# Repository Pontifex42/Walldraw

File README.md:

# Walldraw
Vollständige Anleitung auf Deutsch ist in "Wandplotter.pdf".
Find a german manual in the file "Wandplotter.pdf".

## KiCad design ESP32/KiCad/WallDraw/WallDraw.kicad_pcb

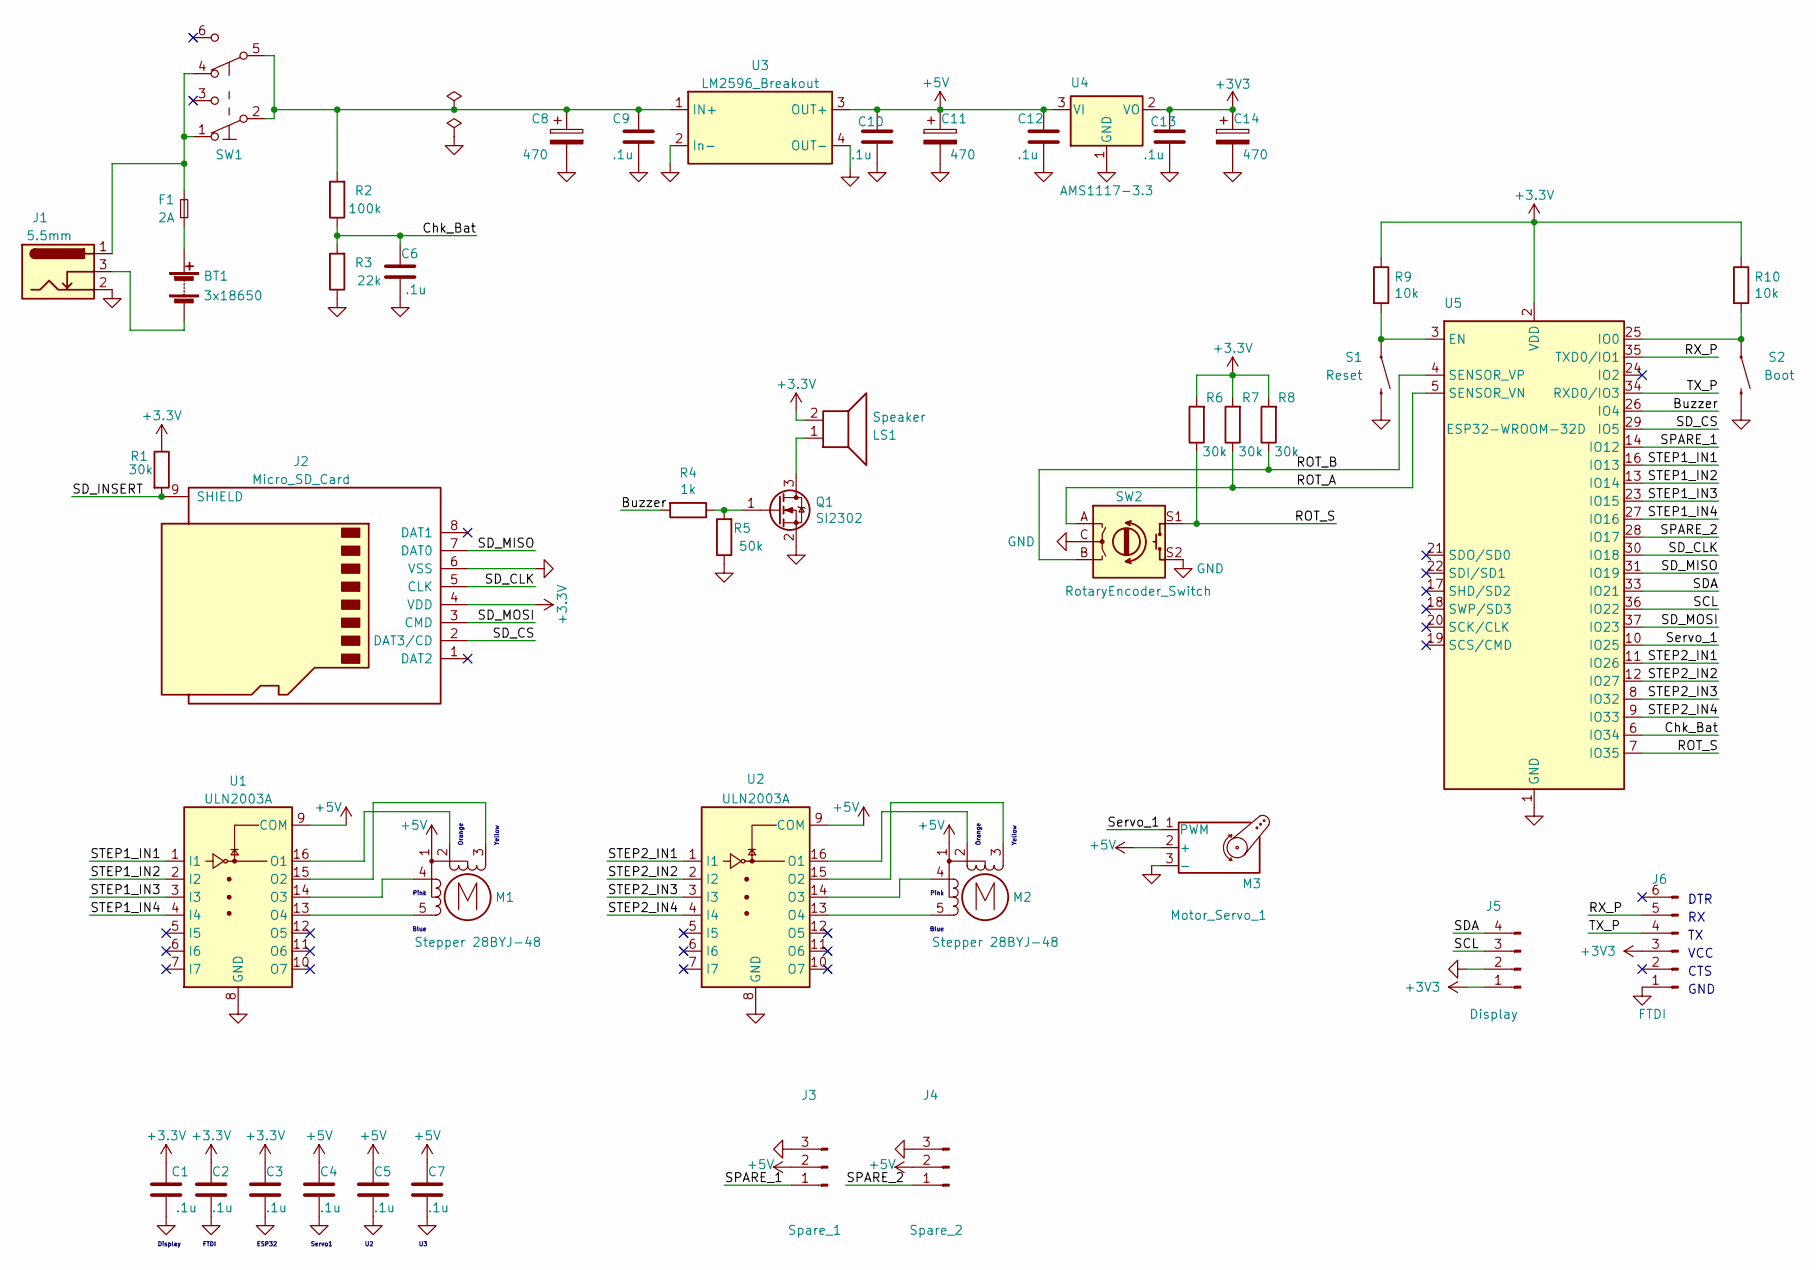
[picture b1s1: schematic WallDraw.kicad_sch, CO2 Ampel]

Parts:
BT1: 3x18650; LiIo18650x3_PCB_Mount
C1, C2, C3, C4, C5, C6, C7, C9, C10, C12, C13: .1u; C_0805_2012Metric_Pad1.18x1.45mm_HandSolder
C8, C11, C14: 470; CP_Elec_8x10.5
F1: 2A; Fuse_1206_3216Metric_Pad1.42x1.75mm_HandSolder
J1: 5.5mm; BarrelJack_Horizontal
J2: Micro_SD_Card; GCT-MEM2055-00-190-01-A
J3: Spare_1; PinHeader_1x03_P2.54mm_Vertical
J4: Spare_2; PinHeader_1x03_P2.54mm_Vertical
J5: Display; OLED_1.3
J6: FTDI; PinHeader_1x06_P2.54mm_Vertical
LS1: Speaker; HN9650B Buzzer
M1, M2: Stepper 28BYJ-48; JST_EH_B5B-EH-A_1x05_P2.50mm_Vertical
M3: Motor_Servo_1; PinHeader_1x03_P2.54mm_Vertical
Q1: SI2302; SOT-23
R1, R6, R7, R8: 30k; R_0805_2012Metric_Pad1.20x1.40mm_HandSolder
R2: 100k; R_0805_2012Metric_Pad1.20x1.40mm_HandSolder
R3: 22k; R_0805_2012Metric_Pad1.20x1.40mm_HandSolder
R4: 1k; R_0805_2012Metric_Pad1.20x1.40mm_HandSolder
R5: 50k; R_0805_2012Metric_Pad1.20x1.40mm_HandSolder
R9, R10: 10k; R_0805_2012Metric_Pad1.20x1.40mm_HandSolder
S1: Reset; TACTILE_SWITCH_SMD_6.0X3.5MM
S2: Boot; TACTILE_SWITCH_SMD_6.0X3.5MM
SW1: SW_Push_DPDT; PS-22F02
SW2: RotaryEncoder_Switch; EC11_Rotary_SMD
U1, U2: ULN2003A; SOP-16_3.9x9.9mm_P1.27mm
U3: LM2596_Breakout; BuckConverter_LM2596_Breakout
U4: AMS1117-3.3; SOT-223-3_TabPin2
U5: ESP32-WROOM-32D; ESP32-WROOM-32

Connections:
+5V: C4.1, C5.1, C7.1, C10.1, C11.1, C12.1, J3.2, J4.2, M1.1, M2.1, M3.2 (+), U1.9 (COM), U2.9 (COM), U3.3 (OUT+), U4.3 (VI)
/Buzzer: R4.2, U5.26 (IO4)
/Chk_Bat: C6.1, R2.1, R3.2, U5.6 (IO34)
/ROT_A: R7.1, SW2.A, U5.5 (SENSOR_VN)
/ROT_B: R8.1, SW2.B, U5.4 (SENSOR_VP)
/ROT_S: R6.1, SW2.S1, U5.7 (IO35)
/RX_P: J6.5, U5.35 (TXD0/IO1)
/SCL: J5.3, U5.36 (IO22)
/SDA: J5.4, U5.33 (IO21)
/SD_CLK: J2.5 (CLK), U5.30 (IO18)
/SD_CS: J2.2 (DAT3/CD), U5.29 (IO5)
/SD_INSERT: J2.9 (SHIELD), R1.2
/SD_MISO: J2.7 (DAT0), U5.31 (IO19)
/SD_MOSI: J2.3 (CMD), U5.37 (IO23)
/SPARE_1: J3.1, U5.14 (IO12)
/SPARE_2: J4.1, U5.28 (IO17)
/STEP1_IN1: U1.1 (I1), U5.16 (IO13)
/STEP1_IN2: U1.2 (I2), U5.13 (IO14)
/STEP1_IN3: U1.3 (I3), U5.23 (IO15)
/STEP1_IN4: U1.4 (I4), U5.27 (IO16)
/STEP2_IN1: U2.1 (I1), U5.11 (IO26)
/STEP2_IN2: U2.2 (I2), U5.12 (IO27)
/STEP2_IN3: U2.3 (I3), U5.8 (IO32)
/STEP2_IN4: U2.4 (I4), U5.9 (IO33)
/Servo_1: M3.1 (PWM), U5.10 (IO25)
/TX_P: J6.4, U5.34 (RXD0/IO3)
GND: C1.2, C2.2, C3.2, C4.2, C5.2, C6.2, C7.2, C8.2, C9.2, C10.2, C11.2, C12.2, C13.2, C14.2, J1.2, J2.6 (VSS), J3.3, J4.3, J5.2, J6.1, M3.3 (-), Q1.2 (S), R3.1, R5.1, S1.2, S2.2, SW2.C, SW2.S2, U1.8 (GND), U2.8 (GND), U3.2 (In-), U3.4 (OUT-), U4.1 (GND), U5.1 (GND), U5.15 (GND), U5.38 (GND), U5.39 (GND)
unnamed: BT1.1 (+), F1.1
unnamed: BT1.6 (-), J1.3
unnamed: C8.1, C9.1, R2.2, SW1.2, SW1.5, U3.1 (IN+)
unnamed: F1.2, J1.1, SW1.1, SW1.4
unnamed: LS1.1, Q1.3 (D)
unnamed: M1.2, U1.16 (O1)
unnamed: M1.3 (-), U1.15 (O2)
unnamed: M1.4, U1.14 (O3)
unnamed: M1.5, U1.13 (O4)
unnamed: M2.2, U2.16 (O1)
unnamed: M2.3 (-), U2.15 (O2)
unnamed: M2.4, U2.14 (O3)
unnamed: M2.5, U2.13 (O4)
unnamed: Q1.1 (G), R4.1, R5.2
unnamed: R9.2, S1.1, U5.3 (EN)
unnamed: R10.2, S2.1, U5.25 (IO0)

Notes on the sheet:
CTS
Yellow
Pink
Blue
VCC
ESP32
Orange
Display
GND
FTDI
DTR
Servo1

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
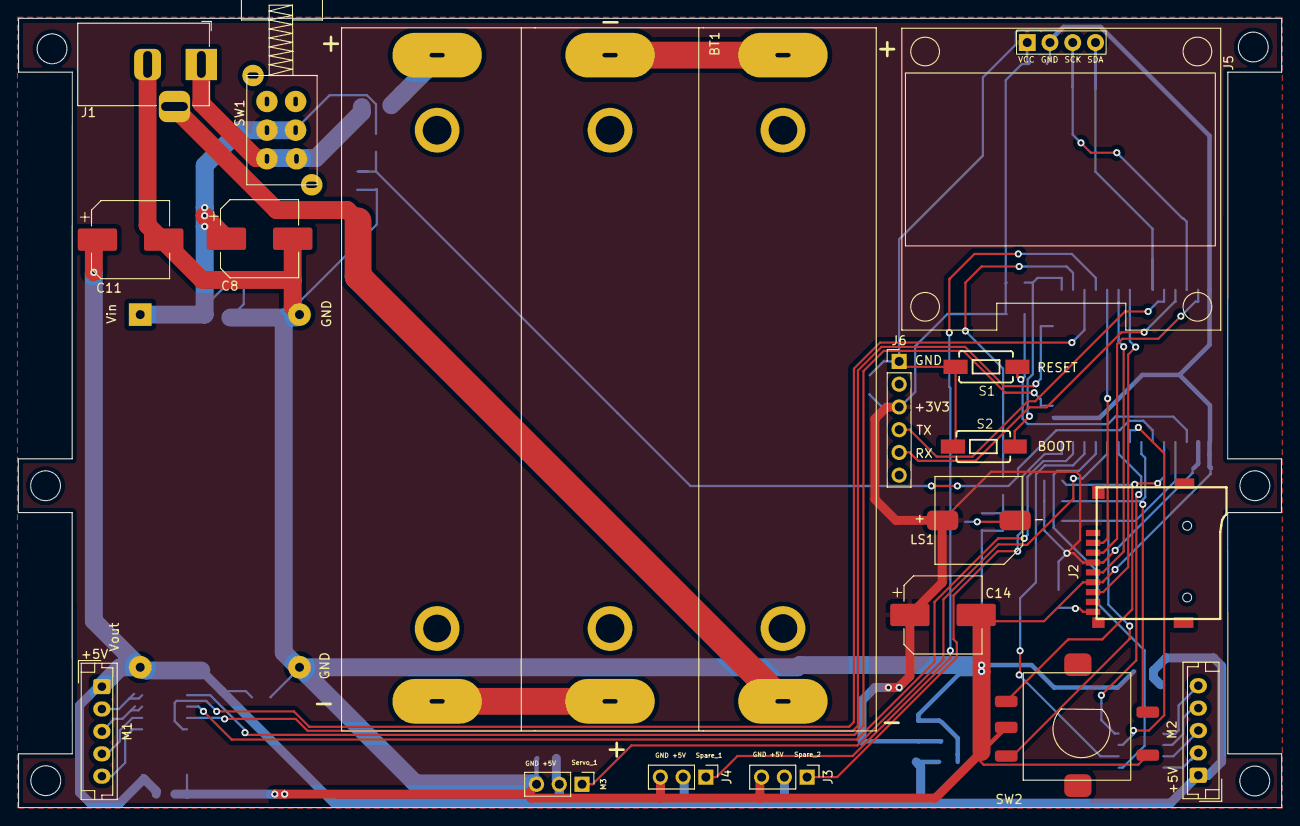
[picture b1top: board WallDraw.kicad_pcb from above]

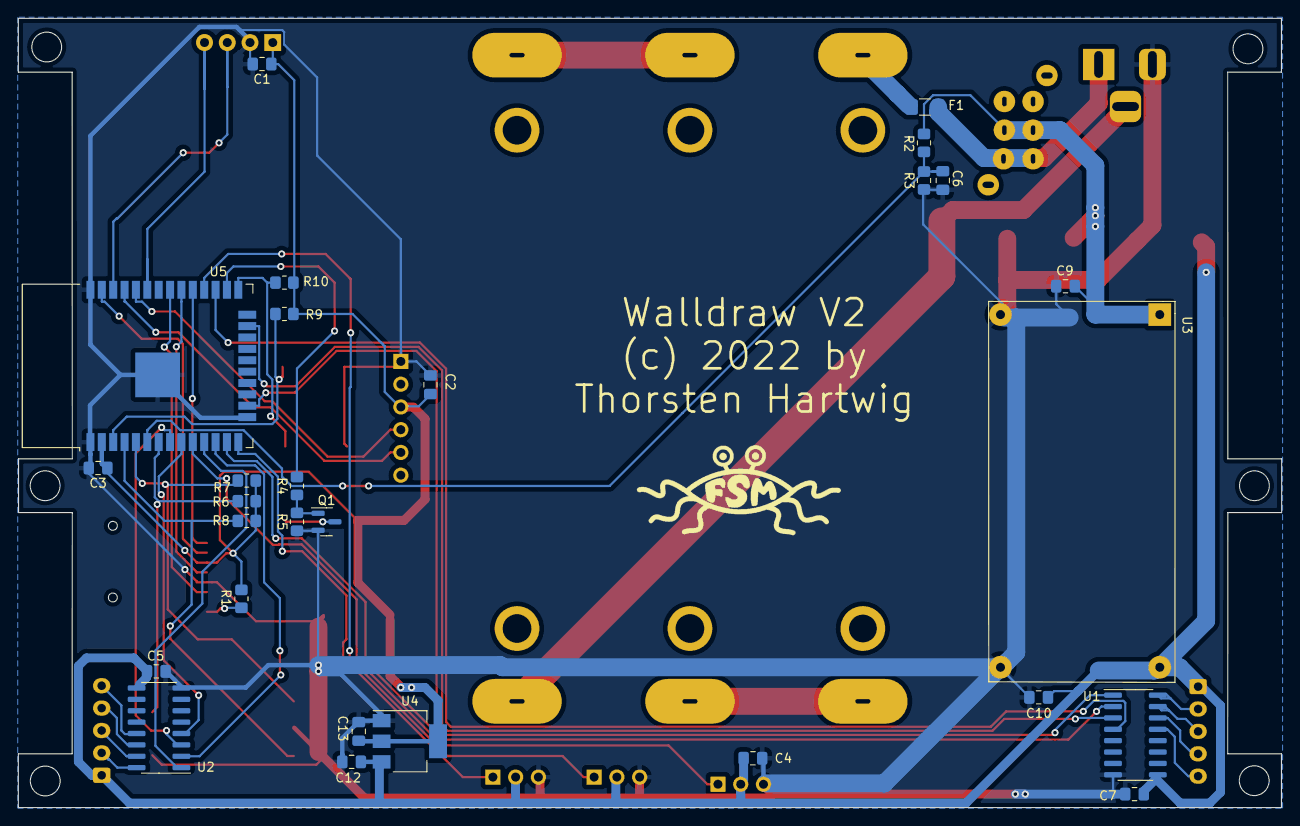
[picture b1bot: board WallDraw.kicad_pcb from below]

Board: 2 copper layers, 141.0 x 88.1 mm, 46 parts (28 on the bottom side), 44 nets.

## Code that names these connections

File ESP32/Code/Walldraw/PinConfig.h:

#pragma once
#include "Arduino.h"

// Rotary encoder
#define PIN_ROT_A	39 // SVN
#define PIN_ROT_B	36 // SVP 
#define PIN_ROT_S	35

// Display 1302
#define PIN_I2C_SDA		21
#define PIN_I2C_SCL		22

// Servo
#define PIN_SERVO1_PULSE 25

// Overdischarge protection
#define PIN_CHECK_BATT	34

// Stepper
#define PIN_STEPPER_L_IN1 13
#define PIN_STEPPER_L_IN2 14
#define PIN_STEPPER_L_IN3 15
#define PIN_STEPPER_L_IN4 16

#define PIN_STEPPER_R_IN1 26
#define PIN_STEPPER_R_IN2 27
#define PIN_STEPPER_R_IN3 32
#define PIN_STEPPER_R_IN4 33

// Micro SD Card
#define PIN_SD_MOSI	23
#define PIN_SD_MISO	19
#define PIN_SD_CS	5
#define PIN_SD_SCK	18

// Buzzer
#define PIN_BUZZER	4

// Spare pins
#define PIN_SPARE_1	12
#define PIN_SPARE_2	17

#define DEBUG_PRINTLN(a) Serial.println(a)
//#define DEBUG_PRINTLN(a)
#define DEBUG_PRINT(a) Serial.print(a)
//#define DEBUG_PRINT(a)

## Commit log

2022-08-14 Smaller fix regarding random y-offsets

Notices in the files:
ESP32/KiCad/WallDraw/WallDraw.kicad_pcb:
(c) 2022 by
Thorsten Hartwig
